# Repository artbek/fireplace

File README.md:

Fireplace (Christmas Ornament)
==============================

Video: https://youtu.be/tF_NVPfcYiw

<br />

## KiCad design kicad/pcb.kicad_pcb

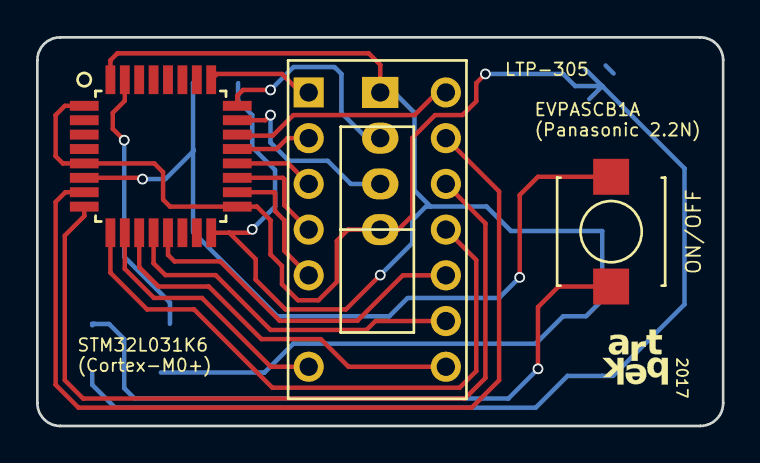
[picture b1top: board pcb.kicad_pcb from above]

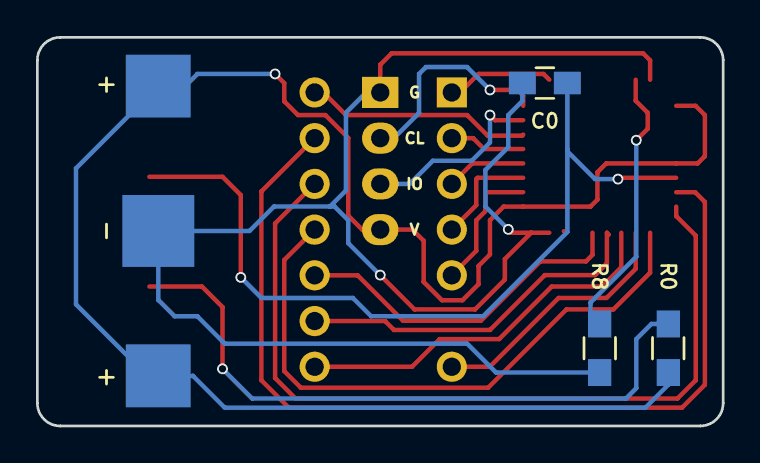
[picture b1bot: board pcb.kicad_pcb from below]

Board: 2 copper layers, 38.1 x 21.6 mm, 8 parts (4 on the bottom side), 20 nets.

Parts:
BT0: Battery_Cell; BatteryHolder_1220
C0: 100nF; C_0805_HandSoldering
J0: Conn_01x04; SWD_PROGRAMMING_HEADER
ON/OFF: ON_OFF; SW_PANASONIC
R0, R8: 2k; R_0805_HandSoldering
S0: 5x7_DISPLAY_LTP-305; 2x7_dot_matrix
U0: STM32L031x4/6; TQFP-32_7x7mm_Pitch0.8mm

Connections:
+3V3: BT0.1, J0.4, R0.1, U0.1, U0.5, U0.17
GND: BT0.2, C0.2, J0.1, R8.1, U0.16, U0.32
unnamed: C0.1, ON/OFF.1, U0.6
unnamed: J0.2, U0.24
unnamed: J0.3, U0.23
unnamed: ON/OFF.2, R0.2
unnamed: R8.2, U0.31
unnamed: S0.1C, U0.25
unnamed: S0.2, U0.21
unnamed: S0.3, U0.20
unnamed: S0.4, U0.19
unnamed: S0.5C, U0.18
unnamed: S0.7, U0.10
unnamed: S0.8C, U0.11
unnamed: S0.9, U0.12
unnamed: S0.10, U0.13
unnamed: S0.11, U0.9
unnamed: S0.12, U0.8
unnamed: S0.13C, U0.7
unnamed: S0.14C, U0.22

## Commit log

2017-11-18 Initial.
2017-11-19 Working flame.
2017-11-26 Final model.
2018-01-07 README.md
2020-02-24 Update README (fix video link).
